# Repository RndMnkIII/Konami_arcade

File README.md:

# Konami_arcade

Hello everyone, I created this repository to share it with other people interested in preserving Konami's arcade boards in the form of core for FPGA. All the material I collect as well as my own developments will be uploaded to the repository. I would like the authorship of the material to be recognized if someone considers it useful for their own developments.

## Developments:

### Aliens arcade board

#### Custom IC's pinout documentation:

I've created this PDF with a description of the IC's as I found on the Aliens arcade board:
https://github.com/RndMnkIII/Konami_arcade/blob/master/Aliens/Documentation/konami_custom_ICs_Aliens.pdf

I have also included photographs of the IC's to facilitate the identification of the pins for pickling these chips. I should be grateful for the help provided to [@furrtek](https://twitter.com/furrtek?s=17) in this regard, as it is collaborating to reverse engineer the operation of these circuits.

#### Konami-2 nano adapter v1.2:

I have developed a pcb to be able to debug the signals of the konami-2 cpu (052526) using the FPGA DE10-Nano, it is simply an appropriate interface to route the signals from the cpu pins to the GPIO1 connector of the FPGA by a bidirectional conversion of TTL 5v and CMOS 3.3v levels.

All the schematics of the Kicad version 5.1 board are available in the repository for download, as well as the step files with the 3d models that are not in the standard Kicad library that I have used for the footprints of the components.

Schematic:
https://github.com/RndMnkIII/Konami_arcade/blob/master/Aliens/custom_pcbs/Konami-2_DE10Nano_adapter_V1_2/Konami-2_DE10Nano_adapter_V1_2.pdf

### Added 07/10/2019: PAL IC's verilog code:
https://github.com/RndMnkIII/Konami_arcade/blob/master/Aliens/verilog/PAL16L8_053327-D20.v
https://github.com/RndMnkIII/Konami_arcade/blob/master/Aliens/verilog/PAL16L8_053326-D21.v

### Added 08/10/2019: PAL IC's Test benchs and GTKWave visualizations:

### Added 11/11/2019: Socketed board with test points labels:

### Added 28/05/2020: Aliens (non merged Rom Set 3) MRA for MiSTer:
https://github.com/RndMnkIII/Konami_arcade/blob/master/Aliens/hardware/roms/aliens3.mra

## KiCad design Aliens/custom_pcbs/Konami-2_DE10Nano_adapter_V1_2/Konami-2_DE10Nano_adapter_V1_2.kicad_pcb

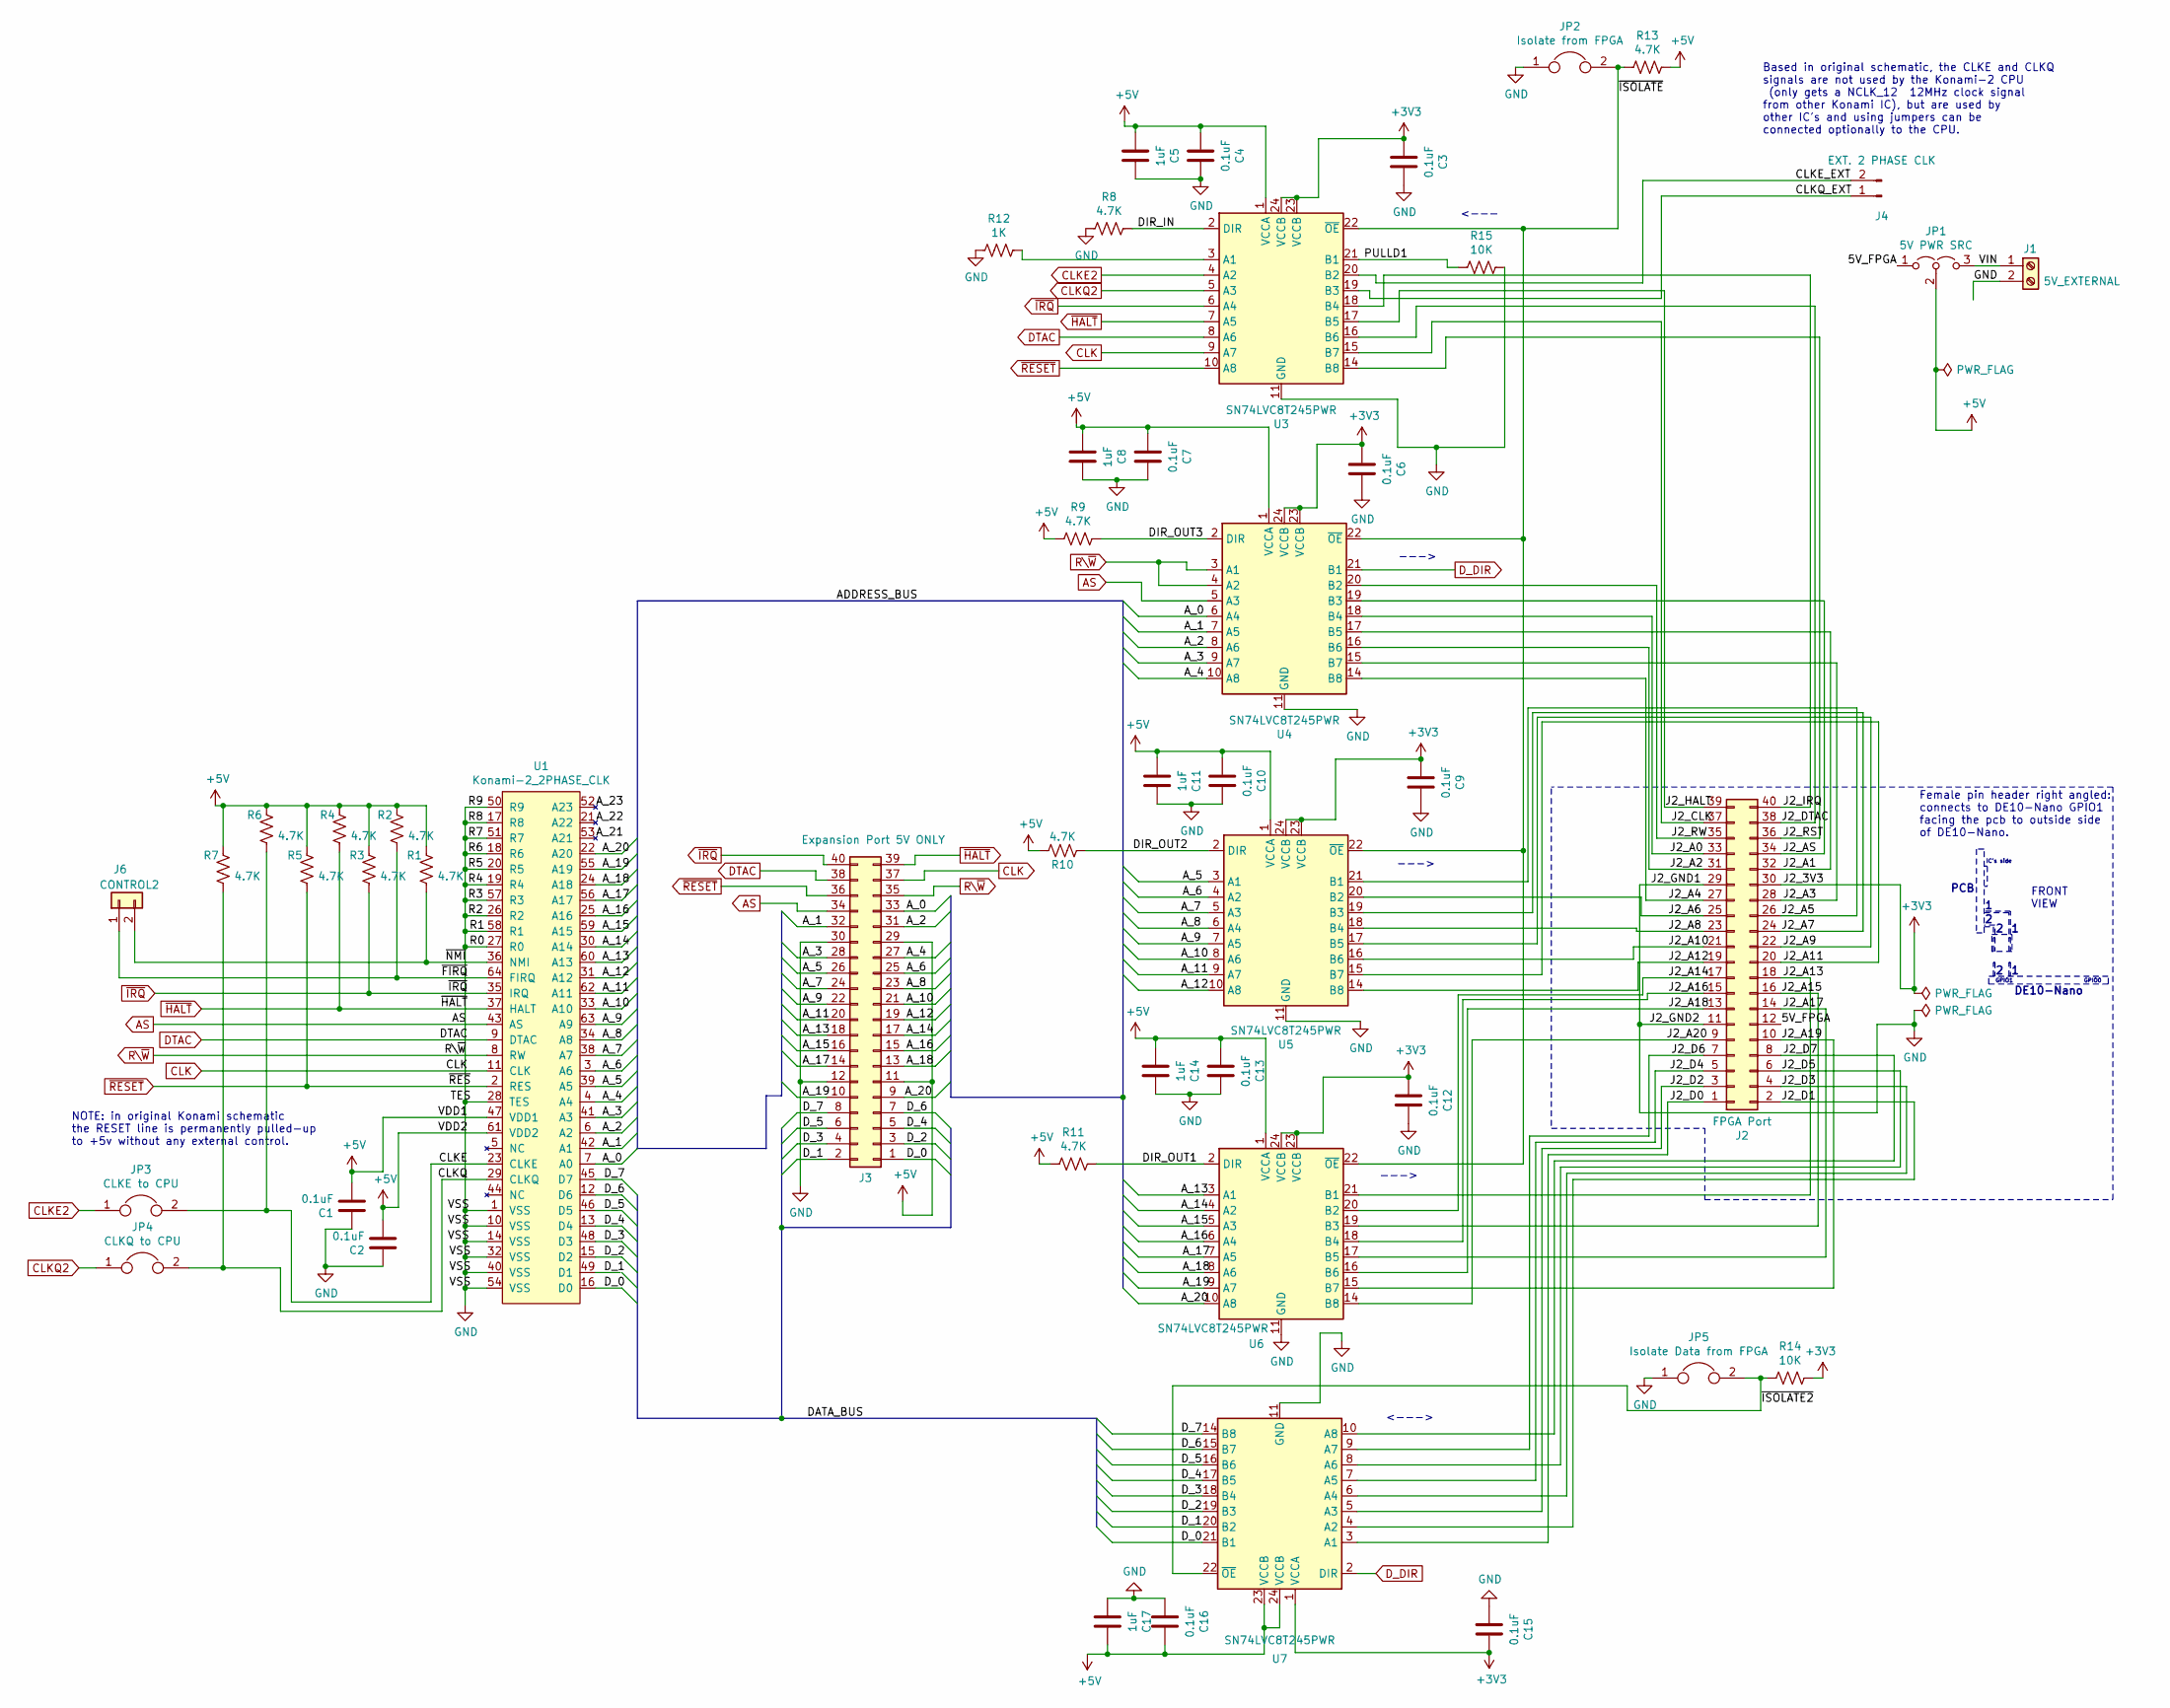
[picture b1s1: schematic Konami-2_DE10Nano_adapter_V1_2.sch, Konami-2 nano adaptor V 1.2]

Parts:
C1, C2, C3, C4, C6, C7, C9, C10, C12, C13, C15, C16: 0.1uF; C_Polyester_D3.8mm_W2.6mm_P2.50mm
C5, C8, C11, C14, C17: 1uF; C_Polyester_D3.8mm_W2.6mm_P2.50mm
J1: 5V_EXTERNAL; TerminalBlock_Altech_AK300-2_P5.00mm
J2: FPGA Port; Pin_Header_Straight_2x20_Pitch2.54mm
J3: Expansion Port 5V ONLY; Pin_Header_Straight_2x20_Pitch2.54mm
J4: EXT. 2 PHASE CLK; Pin_Header_Straight_1x02_Pitch2.54mm
J6: CONTROL2; Pin_Header_Straight_1x02_Pitch2.54mm
JP1: 5V PWR SRC; Pin_Header_Straight_1x03_Pitch2.54mm
JP2: Isolate from FPGA; Pin_Header_Straight_1x02_Pitch2.54mm
JP3: CLKE to CPU; Pin_Header_Straight_1x02_Pitch2.54mm
JP4: CLKQ to CPU; Pin_Header_Straight_1x02_Pitch2.54mm
JP5: Isolate Data from FPGA; Pin_Header_Straight_1x02_Pitch2.54mm
R1, R2, R3, R4, R5, R6, R7, R8, R9, R10, R11, R13: 4.7K; R_Axial_DIN0204_L3.6mm_D1.6mm_P5.08mm_Horizontal
R12: 1K; R_Axial_DIN0204_L3.6mm_D1.6mm_P5.08mm_Horizontal
R14, R15: 10K; R_Axial_DIN0204_L3.6mm_D1.6mm_P5.08mm_Horizontal
U1: Konami-2_2PHASE_CLK; KONAMI-2_64_PGA
U3, U4, U5, U6, U7: SN74LVC8T245PWR; TSSOP-24_SN74LVC8T245PWR

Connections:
+3V3: C3.2, C6.2, C9.2, C12.2, C15.2, J2.30, R14.2, U3.23 (VCCB), U3.24 (VCCB), U4.23 (VCCB), U4.24 (VCCB), U5.23 (VCCB), U5.24 (VCCB), U6.23 (VCCB), U6.24 (VCCB), U7.1 (VCCA)
+5V: C1.2, C2.2, C4.2, C5.2, C7.2, C8.2, C10.2, C11.2, C13.2, C14.2, C16.2, C17.2, J3.11, J3.29, JP1.2 (C), R1.1, R2.1, R3.1, R4.1, R5.1, R6.1, R7.1, R9.2, R10.2, R11.2, R13.2, U1.47 (VDD1), U1.61 (VDD2), U3.1 (VCCA), U4.1 (VCCA), U5.1 (VCCA), U6.1 (VCCA), U7.23 (VCCB), U7.24 (VCCB)
/5V_FPGA: J2.12, JP1.1 (A)
/A_0: J3.33, U1.7 (A0), U4.6 (A4)
/A_1: J3.32, U1.42 (A1), U4.7 (A5)
/A_2: J3.31, U1.6 (A2), U4.8 (A6)
/A_3: J3.28, U1.41 (A3), U4.9 (A7)
/A_4: J3.27, U1.4 (A4), U4.10 (A8)
/A_5: J3.26, U1.39 (A5), U5.3 (A1)
/A_6: J3.25, U1.3 (A6), U5.4 (A2)
/A_7: J3.24, U1.38 (A7), U5.5 (A3)
/A_8: J3.23, U1.34 (A8), U5.6 (A4)
/A_9: J3.22, U1.63 (A9), U5.7 (A5)
/A_10: J3.21, U1.33 (A10), U5.8 (A6)
/A_11: J3.20, U1.62 (A11), U5.9 (A7)
/A_12: J3.19, U1.31 (A12), U5.10 (A8)
/A_13: J3.18, U1.60 (A13), U6.3 (A1)
/A_14: J3.17, U1.30 (A14), U6.4 (A2)
/A_15: J3.16, U1.59 (A15), U6.5 (A3)
/A_16: J3.15, U1.25 (A16), U6.6 (A4)
/A_17: J3.14, U1.56 (A17), U6.7 (A5)
/A_18: J3.13, U1.24 (A18), U6.8 (A6)
/A_19: J3.10, U1.55 (A19), U6.9 (A7)
/A_20: J3.9, U1.22 (A20), U6.10 (A8)
/A_21: U1.53 (A21)
/A_22: U1.21 (A22)
/A_23: U1.52 (A23)
/CLKE: JP3.2, R6.2, U1.23 (CLKE)
/CLKE_EXT: J4.2, U3.20 (B2)
/CLKQ: JP4.2, R7.2, U1.29 (CLKQ)
/CLKQ_EXT: J4.1, U3.19 (B3)
/DIR_IN: R8.2, U3.2 (DIR)
/DIR_OUT1: R11.1, U6.2 (DIR)
/DIR_OUT2: R10.1, U5.2 (DIR)
/DIR_OUT3: R9.1, U4.2 (DIR)
/D_0: J3.1, U1.16 (D0), U7.21 (B1)
/D_1: J3.2, U1.49 (D1), U7.20 (B2)
/D_2: J3.3, U1.15 (D2), U7.19 (B3)
/D_3: J3.4, U1.48 (D3), U7.18 (B4)
/D_4: J3.5, U1.13 (D4), U7.17 (B5)
/D_5: J3.6, U1.46 (D5), U7.16 (B6)
/D_6: J3.7, U1.12 (D6), U7.15 (B7)
/D_7: J3.8, U1.45 (D7), U7.14 (B8)
/J2_A0: J2.33, U4.18 (B4)
/J2_A1: J2.32, U4.17 (B5)
/J2_A2: J2.31, U4.16 (B6)
/J2_A3: J2.28, U4.15 (B7)
/J2_A4: J2.27, U4.14 (B8)
/J2_A5: J2.26, U5.21 (B1)
/J2_A6: J2.25, U5.20 (B2)
/J2_A7: J2.24, U5.19 (B3)
/J2_A8: J2.23, U5.18 (B4)
/J2_A9: J2.22, U5.17 (B5)
/J2_A10: J2.21, U5.16 (B6)
/J2_A11: J2.20, U5.15 (B7)
/J2_A12: J2.19, U5.14 (B8)
/J2_A13: J2.18, U6.21 (B1)
/J2_A14: J2.17, U6.20 (B2)
/J2_A15: J2.16, U6.19 (B3)
/J2_A16: J2.15, U6.18 (B4)
/J2_A17: J2.14, U6.17 (B5)
/J2_A18: J2.13, U6.16 (B6)
/J2_A19: J2.10, U6.15 (B7)
/J2_A20: J2.9, U6.14 (B8)
/J2_AS: J2.34, U4.19 (B3)
/J2_CLK: J2.37, U3.15 (B7)
/J2_D0: J2.1, U7.3 (A1)
/J2_D1: J2.2, U7.4 (A2)
/J2_D2: J2.3, U7.5 (A3)
/J2_D3: J2.4, U7.6 (A4)
/J2_D4: J2.5, U7.7 (A5)
/J2_D5: J2.6, U7.8 (A6)
/J2_D6: J2.7, U7.9 (A7)
/J2_D7: J2.8, U7.10 (A8)
/J2_DTAC: J2.38, U3.16 (B6)
/J2_HALT: J2.39, U3.17 (B5)
/J2_IRQ: J2.40, U3.18 (B4)
/J2_RST: J2.36, U3.14 (B8)
/J2_RW: J2.35, U4.20 (B2)
/PULLD1: R15.2, U3.21 (B1)
/VIN: J1.1, JP1.3 (B)
/~FIRQ: J6.1, R2.2, U1.64 (FIRQ)
/~ISOLATE: JP2.2, R13.1, U3.22 (~OE), U4.22 (~OE), U5.22 (~OE), U6.22 (~OE)
/~ISOLATE2: JP5.2, R14.1, U7.22 (~OE)
/~NMI: J6.2, R1.2, U1.36 (NMI)
AS: J3.34, U1.43 (AS), U4.5 (A3)
CLK: J3.37, U1.11 (CLK), U3.9 (A7)
CLKE2: JP3.1, U3.4 (A2)
CLKQ2: JP4.1, U3.5 (A3)
DTAC: J3.38, U1.9 (DTAC), U3.8 (A6)
D_DIR: U4.21 (B1), U7.2 (DIR)
GND: C1.1, C2.1, C3.1, C4.1, C5.1, C6.1, C7.1, C8.1, C9.1, C10.1, C11.1, C12.1, C13.1, C14.1, C15.1, C16.1, C17.1, J1.2, J2.11, J2.29, J3.12, J3.30, JP2.1, JP5.1, R8.1, R12.1, R15.1, U1.1 (VSS), U1.10 (VSS), U1.14 (VSS), U1.17 (R8), U1.18 (R6), U1.19 (R4), U1.20 (R5), U1.26 (R2), U1.27 (R0), U1.28 (TES), U1.32 (VSS), U1.40 (VSS), U1.50 (R9), U1.51 (R7), U1.54 (VSS), U1.57 (R3), U1.58 (R1), U3.11 (GND), U3.12 (GND), U3.13 (GND), U4.11 (GND), U4.12 (GND), U4.13 (GND), U5.11 (GND), U5.12 (GND), U5.13 (GND), U6.11 (GND), U6.12 (GND), U6.13 (GND), U7.11 (GND), U7.12 (GND), U7.13 (GND)
unnamed: R12.2, U3.3 (A1)
R\~W: J3.35, U1.8 (RW), U4.3 (A1), U4.4 (A2)
~HALT: J3.39, R4.2, U1.37 (HALT), U3.7 (A5)
~IRQ: J3.40, R3.2, U1.35 (IRQ), U3.6 (A4)
~RESET: J3.36, R5.2, U1.2 (RES), U3.10 (A8)

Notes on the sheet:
<---
--->
<--->
NOTE: in original Konami schematic the RESET line is permanently pulled-up to +5v without any external control.
Based in original schematic, the CLKE and CLKQ signals are not used by the Konami-2 CPU (only gets a NCLK_12 12MHz clock signal from other Konami IC), but are used by other IC's and using jumpers can be connected optionally to the CPU.
Female pin header right angled: connects to DE10-Nano GPIO1 facing the pcb to outside side of DE10-Nano.
DE10-Nano
PCB
GPIO1
IC's side
GPIO0
FRONT VIEW

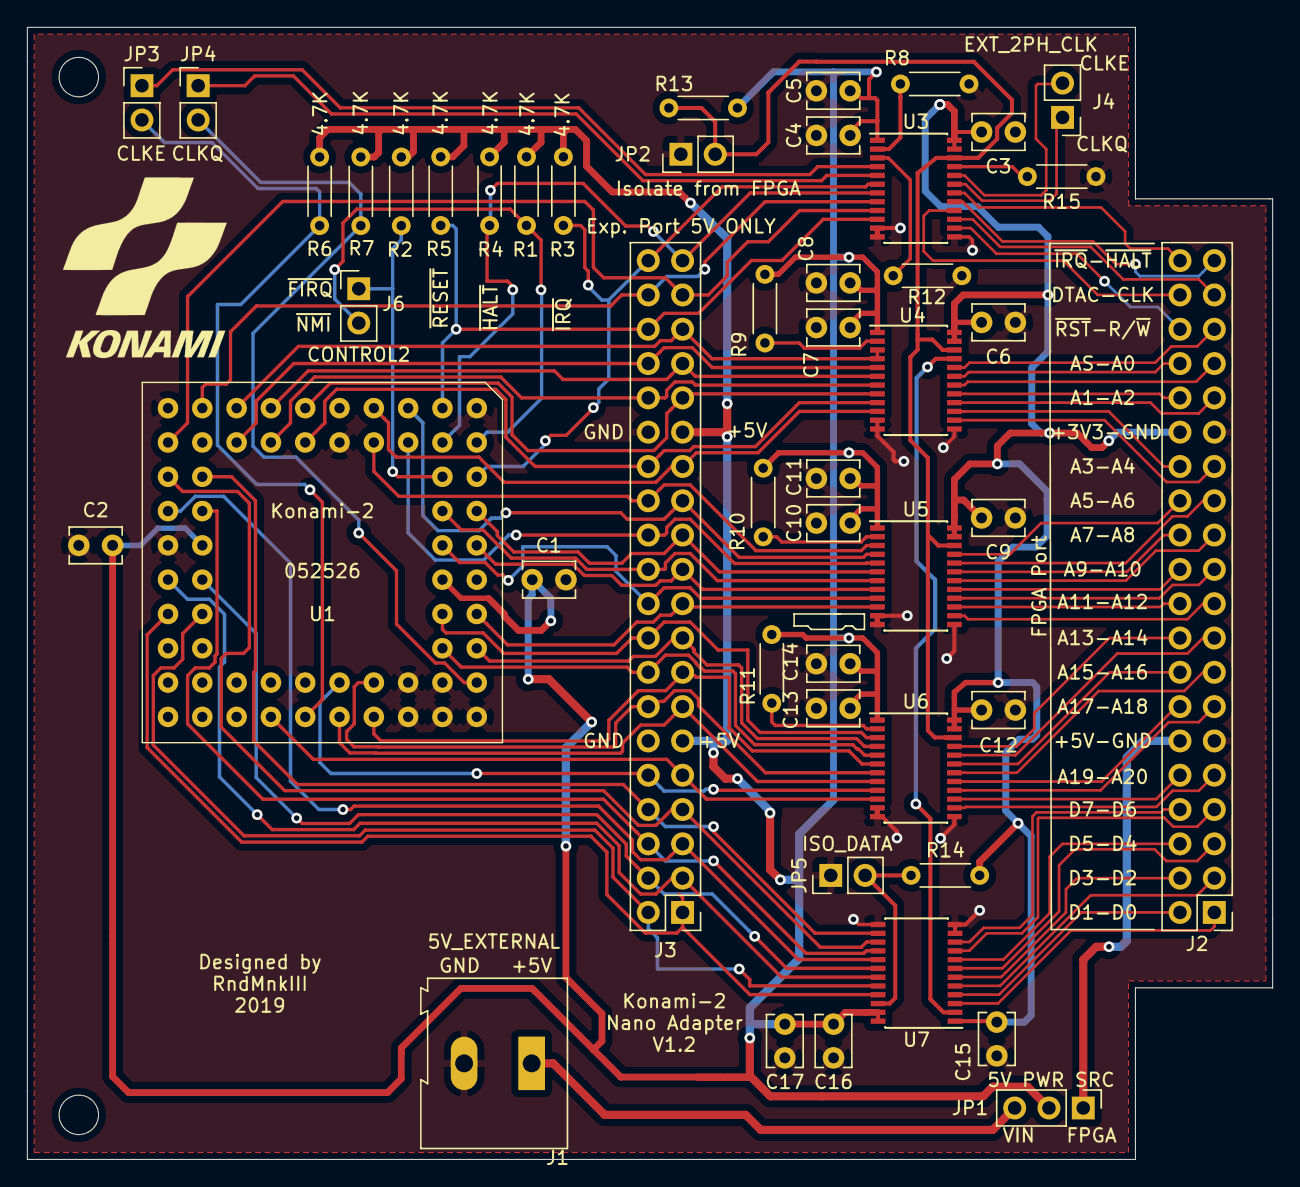
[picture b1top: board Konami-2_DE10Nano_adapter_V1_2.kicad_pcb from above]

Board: 2 copper layers, 92.2 x 83.8 mm, 48 parts (0 on the bottom side), 94 nets.

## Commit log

2019-09-04 Initial commit
    Added documentation of Aliens arcade.
2019-09-04 Updated documentatiion
    Updated documentatiion
2019-09-04 updated documentation
    added photos of custom ic's. Added pinout doc as pdf.
2019-09-04 updated docs folders
    updated docs folders
2019-09-23 uploaded konami-2 pcb nano adapter
    Kicad 15 pcb design of konami-2 cpu to DE10-Nano FPGA adapter.
2019-09-24 Update Gerber_Konami2.zip
    Fixed zip file with gerber files
2019-09-24 Create Konami-2_DE10Nano_adapter.jpg
    update 3d renderring of Konami-2 nano adapter V1.1
2019-09-24 aliens arcade board
    aliens arcade board
2019-09-24 more documents
    more documents
2019-09-26 Konami-2 nano adapter v1.2
    Konami-2 nano adapter v1.2
2019-09-26 Added V1.2 schematic
    Added V1.2 schematic
2019-10-07 Converted PAL equations to Verilog
    Converted PAL equations to Verilog
2019-10-08 PAL16L8_053326_D21 Test Bench and GTKWave savefile
2019-11-09 Oscilloscope image captures
    Global reset and main cpu clock signals.
2019-11-11 Added socketed board images
    Added socketed board images
2019-11-27 PSX2 Dualshock to serial encoder
2020-01-15 Added csv2testbench python script
2020-01-15 updated csv2testbench
2020-01-16 updated bus control schematic
2020-01-23 updated Caius link
2020-01-23 update Caius link
2020-02-14 New Konami aliens romset :aliens4 (World Set 4)
    Added new Aliens romset found in my current arcade pcb board. No special labels in the EPROM IC's that identify this version. Stored in Konami_arcade\Aliens\hardware\eproms\GX875_PWB351864_ROMSET_PCB1
2020-02-14 Changed new aliens romset name
    Changed new aliens romset name to Konami_arcade\Aliens\hardware\eproms\GX875_PWB351864_ROMSET_PCB2_aliens4
2020-05-28 Add files via upload
    Created MRA file for future Konami Aliens core, based on Aliens3.zip non merged romset. I will update the mra for merged sets in the future.
2020-05-28 added MRA file
2020-05-28 Several files update
2020-05-28 Updated ALIENS3.MRA
    Updated aliens3.mra file, with better ROM organization in more logical way (until tested for performance in the real FPGA SDRAM).
    Added information for those interested in the culture of historical hardware.
2020-05-28 Fixed errors in aliens3.mra file and added zip
    Fixed errors in aliens3.mra file and added zip
2020-05-29 FIX aliens3.mra
2020-12-16 Add files via upload
    fixed max. sprite count per scanline. Better visualization.
2020-12-16 Update aliens_sprites_show2.lua
    fixed color table index
2020-12-16 Add files via upload
    added total sprites per frame and maximum sprites per frame statistics
2021-01-20 xxx
    xxx
